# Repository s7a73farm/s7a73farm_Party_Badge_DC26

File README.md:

# s7a73farmsPartyBadge

# Getting Started to program it
```
Modify the tx/Makefile & rx/Makefile 
Line 16: AVRDUDE = avrdude -c usbasp -p t84 -U flash:w:$(PROJECT).hex
Change usbasp to usbtiny or whatever programmer  you are using.
```

## Build Master Badge
```
git clone git@github.com:SocialGeeks/s7a73farmsPartyBadge.git
cd firmware/tx
make clean
make
make upload
```

## Build Slave Badge
```
git clone git@github.com:SocialGeeks/s7a73farmsPartyBadge.git
cd firmware/rx
make clean
make
make upload
```

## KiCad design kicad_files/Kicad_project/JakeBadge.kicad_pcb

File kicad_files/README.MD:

# FILES
---------------------
Gerbers zip

Kicad project zip

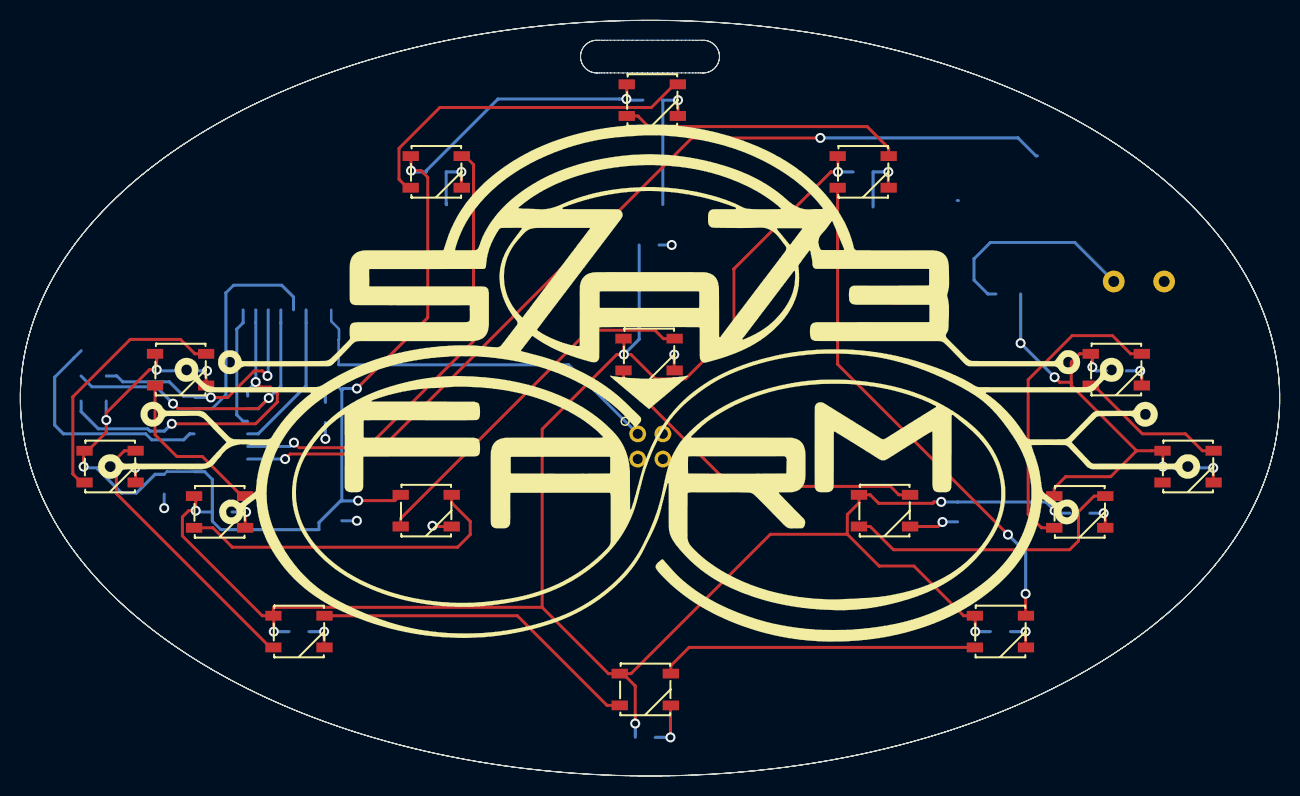
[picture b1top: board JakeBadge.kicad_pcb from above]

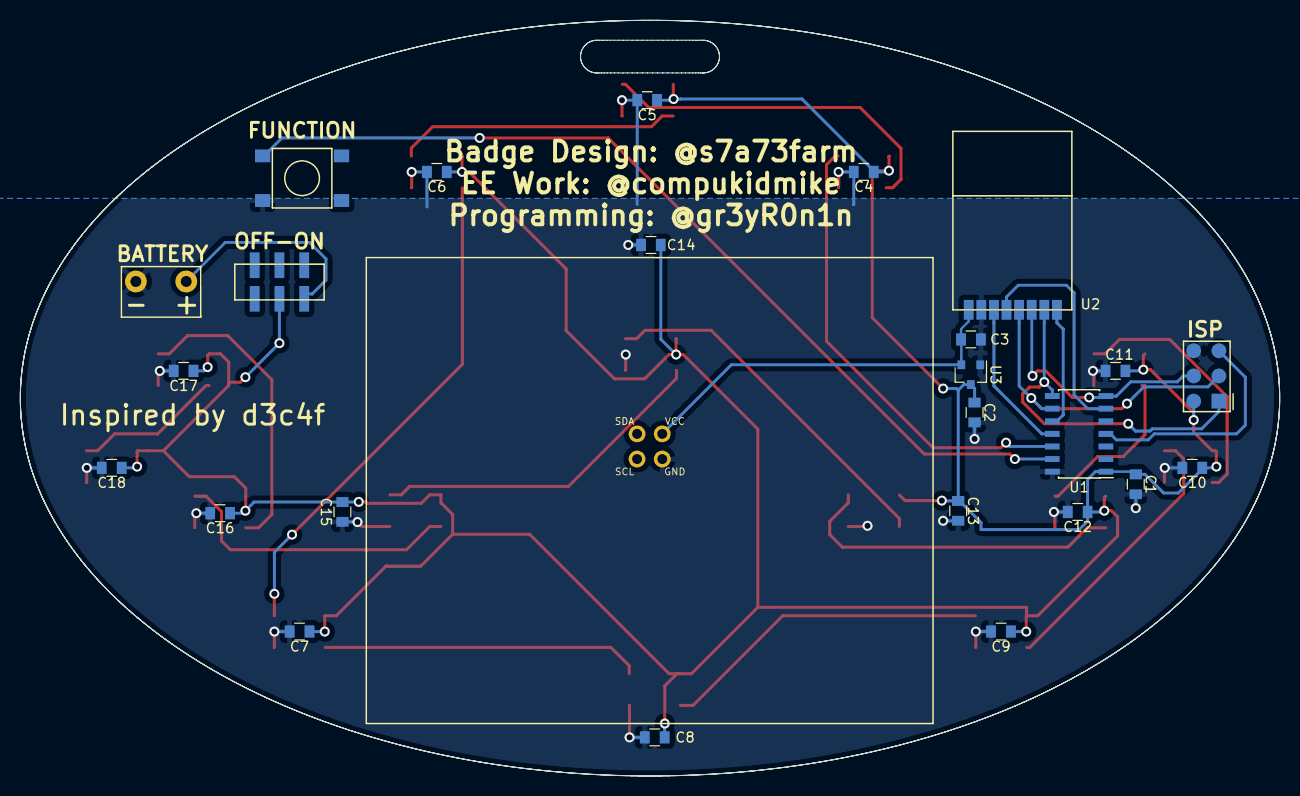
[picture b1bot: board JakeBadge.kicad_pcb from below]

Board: 2 copper layers, 127.0 x 76.2 mm, 41 parts (25 on the bottom side), 27 nets.

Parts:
BT1: Battery; Battery-WireConn
C1, C4, C5, C6, C7, C8, C9, C10, C11, C12, C13, C14, C15, C16, C17, C18: C_Small; C_0805
C2, C3: C; C_0805
CON1: AVR-ISP-6; ISP-AVR-6Pin-SMD
LED1, LED2, LED3, LED4, LED5, LED6, LED7, LED8, LED9, LED10, LED11, LED12, LED13, LED14, LED15: WS2812B
SW1: SW_SPST; JS202011JCQN
SW2: SW_Push; TACT-SMD
U1: ATTINY84A-SSU; SOIC-14_3.9x8.7mm_Pitch1.27mm
U2: NRF24L01; NRF24L01-SMD
U3: MCP1703A-3302_SOT23; SOT-23
X1: Badgelife_shitty_connector; Badgelife-Shitty-2x2

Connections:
+3V3: C3.1, U2.2, U3.2, X1.1
+BATT: C1.1, C2.1, C4.1, C5.1, C6.1, C7.1, C8.1, C9.1, C10.1, C11.1, C12.1, C13.1, C14.1, C15.1, C16.1, C17.1, C18.1, CON1.2, LED1.1, LED2.1, LED3.1, LED4.1, LED5.1, LED6.1, LED7.1, LED8.1, LED9.1, LED10.1, LED11.1, LED12.1, LED13.1, LED14.1, LED15.1, SW1.2, U1.1, U3.3
CE: U1.11, U2.3
CS: U1.6, U2.4
GND: BT1.2, C1.2, C2.2, C3.2, C4.2, C5.2, C6.2, C7.2, C8.2, C9.2, C10.2, C11.2, C12.2, C13.2, C14.2, C15.2, C16.2, C17.2, C18.2, CON1.6, LED1.3, LED2.3, LED3.3, LED4.3, LED5.3, LED6.3, LED7.3, LED8.3, LED9.3, LED10.3, LED11.3, LED12.3, LED13.3, LED14.3, LED15.3, SW2.2, U1.14, U2.1, U3.1, X1.2
IRQ: U1.10, U2.8
LED: LED1.4, U1.12
MISO: CON1.1, U1.8, U2.7
MOSI: CON1.4, U1.7, U2.6
unnamed: BT1.1, SW1.1
unnamed: LED1.2, LED2.4
unnamed: LED2.2, LED3.4
unnamed: LED3.2, LED4.4
unnamed: LED4.2, LED5.4
unnamed: LED5.2, LED6.4
unnamed: LED6.2, LED7.4
unnamed: LED7.2, LED8.4
unnamed: LED8.2, LED9.4
unnamed: LED10.2, LED11.4
unnamed: LED9.2, LED10.4
unnamed: LED11.2, LED12.4
unnamed: LED12.2, LED13.4
unnamed: LED13.2, LED14.4
unnamed: LED14.2, LED15.4
unnamed: SW2.1, U1.13
RST: CON1.5, U1.4
SCK: CON1.3, U1.9, U2.5

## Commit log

2018-08-16 make repo public
2018-08-16 Badge renders
2018-08-16 Gerbers files
2018-08-16 message
